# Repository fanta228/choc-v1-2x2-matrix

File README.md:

# choc-v1-2x2-matrix
Just a project to help me figure out KiCAD.

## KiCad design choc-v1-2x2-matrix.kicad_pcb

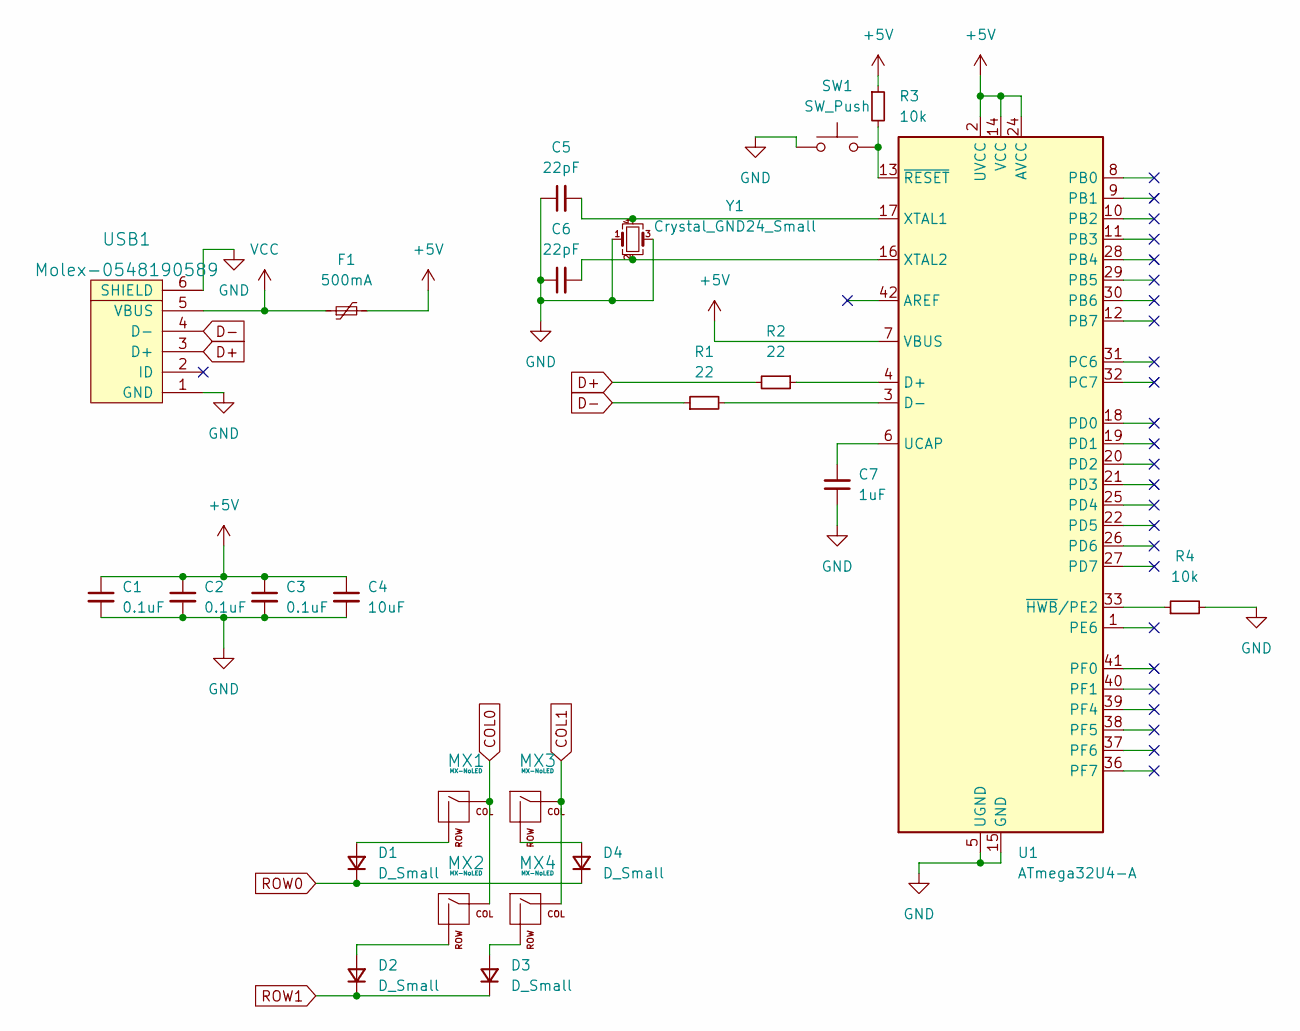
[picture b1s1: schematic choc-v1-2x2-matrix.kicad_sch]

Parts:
C1, C2, C3: 0.1uF; C_0805_2012Metric_Pad1.18x1.45mm_HandSolder
C4: 10uF; C_0805_2012Metric_Pad1.18x1.45mm_HandSolder
C5, C6: 22pF; C_0805_2012Metric_Pad1.18x1.45mm_HandSolder
C7: 1uF; C_0805_2012Metric_Pad1.18x1.45mm_HandSolder
D1, D2, D3, D4: D_Small; D_SOD-123
F1: 500mA; Fuse_0805_2012Metric_Pad1.15x1.40mm_HandSolder
MX1, MX2, MX3, MX4: MX-NoLED; MX-1.5U-NoLED
R1, R2: 22; R_0805_2012Metric_Pad1.20x1.40mm_HandSolder
R3, R4: 10k; R_0805_2012Metric_Pad1.20x1.40mm_HandSolder
SW1: SW_Push; SKQG-1155865
U1: ATmega32U4-A; TQFP-44_10x10mm_P0.8mm
USB1: Molex-0548190589
Y1: Crystal_GND24_Small; Crystal_SMD_3225-4Pin_3.2x2.5mm_HandSoldering

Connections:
+5V: C1.1, C2.1, C3.1, C4.1, F1.2, R3.1, U1.2 (UVCC), U1.7 (VBUS), U1.14 (VCC), U1.24 (AVCC), U1.34 (VCC), U1.44 (AVCC)
COL0: MX1.1 (COL), MX2.1 (COL)
COL1: MX3.1 (COL), MX4.1 (COL)
D+: R2.2, USB1.3 (D+)
D-: R1.1, USB1.4 (D-)
GND: C1.2, C2.2, C3.2, C4.2, C5.1, C6.1, C7.1, R4.2, SW1.1, U1.5 (UGND), U1.15 (GND), U1.23 (GND), U1.35 (GND), U1.43 (GND), USB1.1 (GND), USB1.6 (SHIELD), Y1.1, Y1.3
unnamed: C5.2, U1.17 (XTAL1), Y1.4
unnamed: C6.2, U1.16 (XTAL2), Y1.2
unnamed: C7.2, U1.6 (UCAP)
unnamed: D1.2 (A), MX1.2 (ROW)
unnamed: D2.2 (A), MX2.2 (ROW)
unnamed: D3.2 (A), MX4.2 (ROW)
unnamed: D4.2 (A), MX3.2 (ROW)
unnamed: R1.2, U1.3 (D-)
unnamed: R2.1, U1.4 (D+)
unnamed: R3.2, SW1.2, U1.13 (~RESET)
unnamed: R4.1, U1.33 (~HWB/PE2)
ROW0: D1.1 (K), D4.1 (K)
ROW1: D2.1 (K), D3.1 (K)
VCC: F1.1, USB1.5 (VBUS)

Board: 2 copper layers, 24 parts (16 on the bottom side), 20 nets, no tracks yet.

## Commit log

2023-01-15 First commit.
2023-01-15 Third commit.
2023-01-15 Finished adding all dependencies?
2023-01-15 night 1
2023-01-15 this is looking good thus far
2023-01-15 finished schematic?
2023-01-15 working on the footprint placement
2023-01-16 still working on the footprint placement
2023-01-16 night 2
